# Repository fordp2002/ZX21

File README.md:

# ZX21
40 Years after the Sinclair ZX81 was released this project aims to preserve the first 4 chip computer

This a computer presevation project for the [Sinclair ZX81](https://github.com/fordp2002/ZX21.git).

Features (Hopefully).

* Drop in replacement for a ZX81
* Built in 16K+ RAM, no need for a RAM Pack
* Built in Composite Video Output 
* Barrel Jack power input, center Positive
* OPTION: Single Joystick port (not compatible with quickfire etc.)
* OPTION: Switchable to 1K RAM
* OPTION: [Back Porch Support](http://zx.zigg.net/misc-projects/ZX81_Video_Conditioning.pdf) for early ULAs
* OPTION: Built in support for [ZX-Wespi](https://github.com/holmatic/zx-iot-mi)
* OPTION: [ZON-X](http://www.zx81stuff.org.uk/zx81/hardware/ZONX81) Compatible Yamaha YM2149F Based Sound
* OPTION: Switchable between Sinclair ROM OR [AT28C256 EEPROM](http://ww1.microchip.com/downloads/en/DeviceDoc/doc0006.pdf)
* OPTION: 16 Pin Box Header for DK'Tronics Keyboard

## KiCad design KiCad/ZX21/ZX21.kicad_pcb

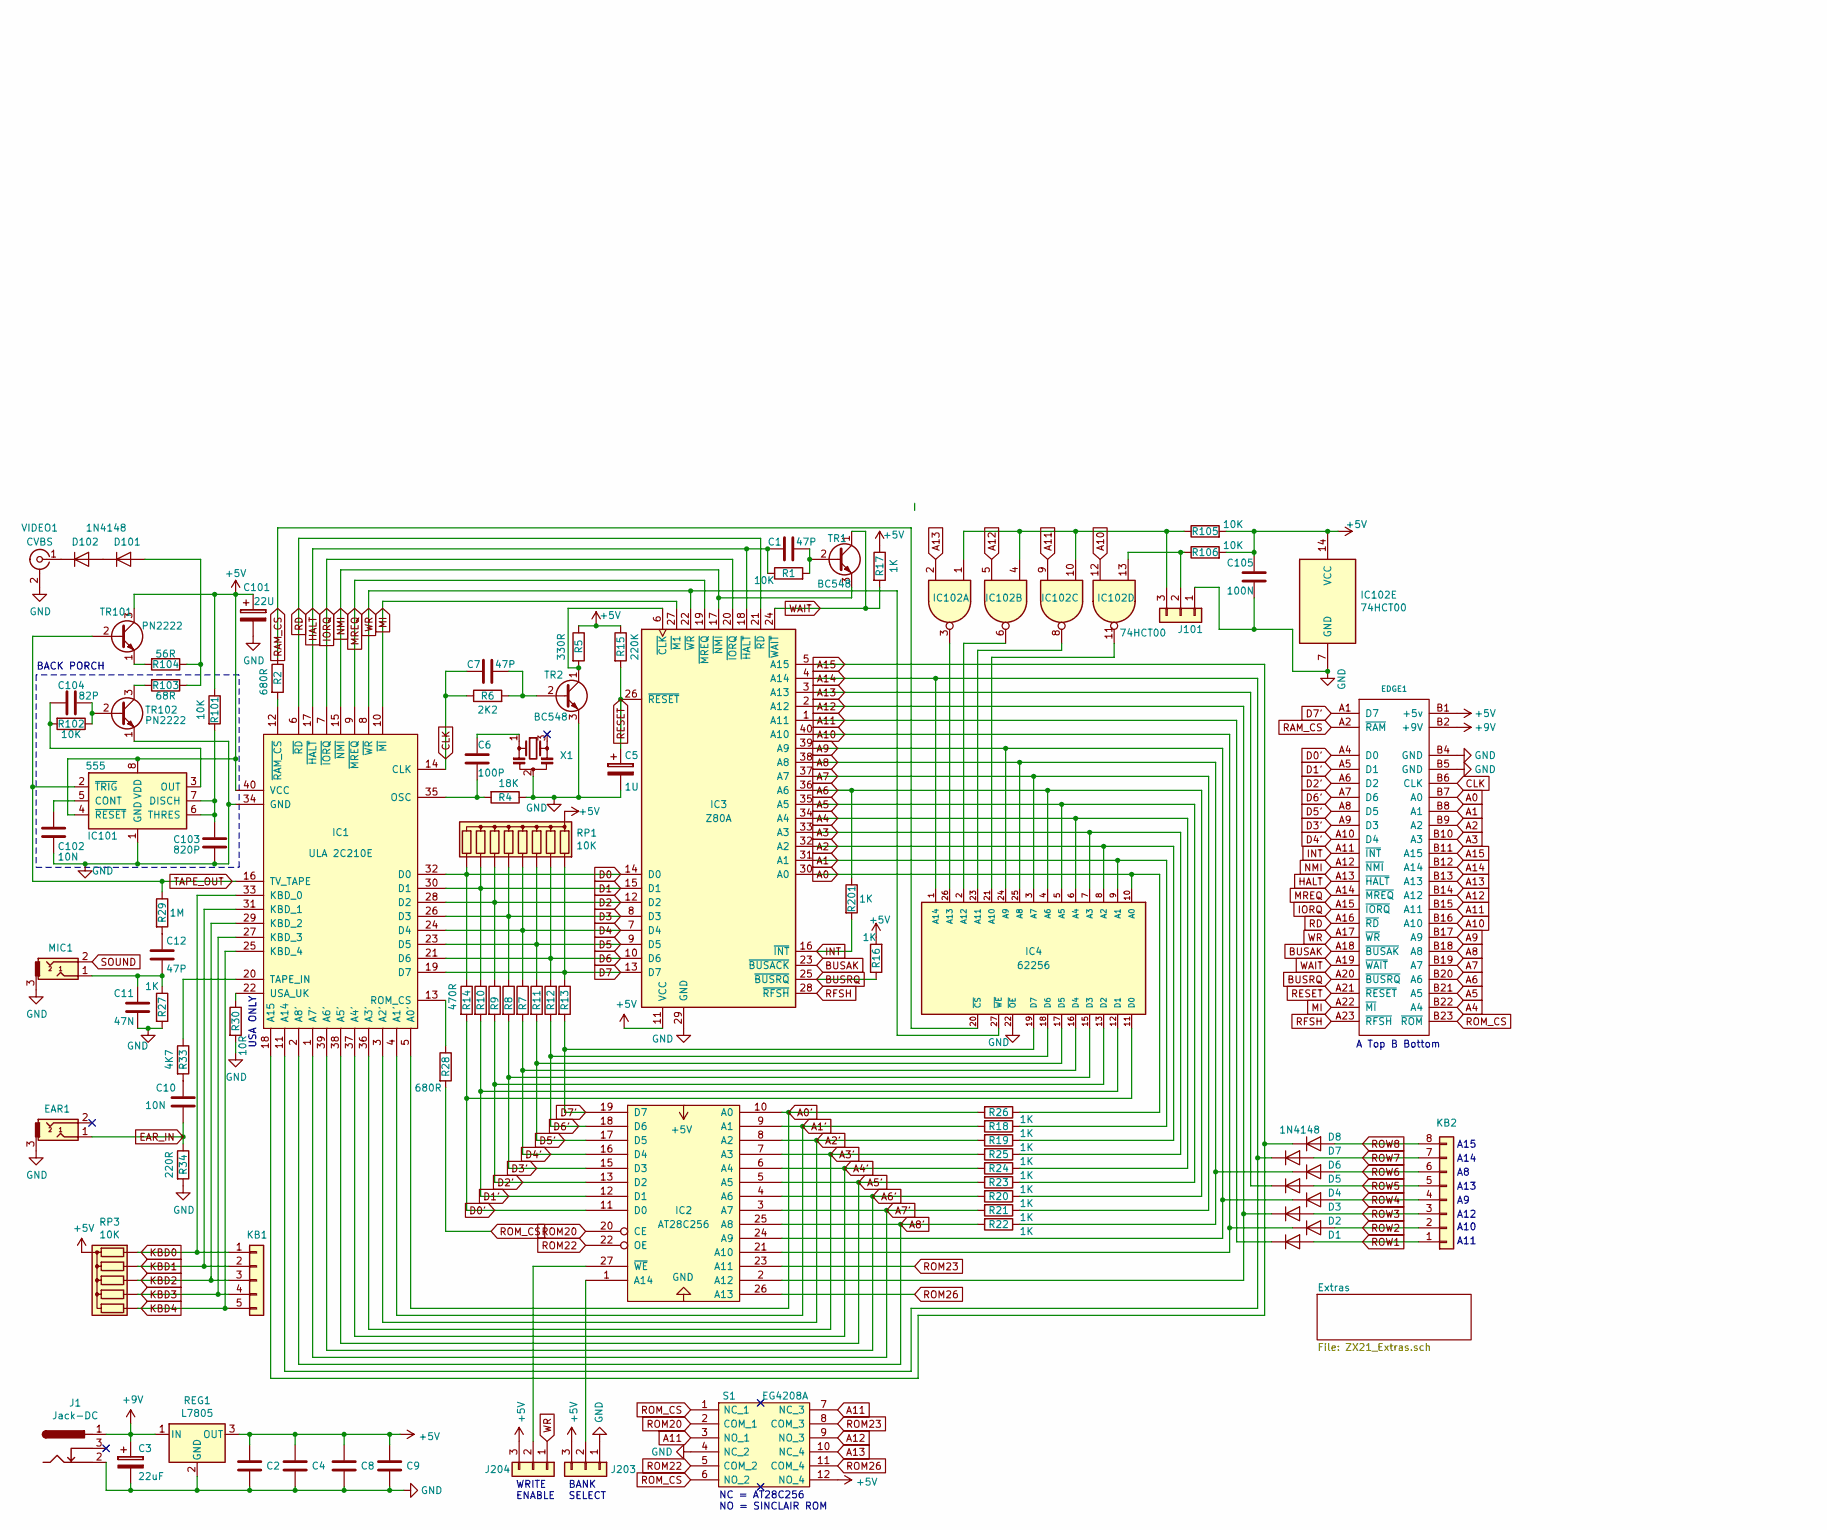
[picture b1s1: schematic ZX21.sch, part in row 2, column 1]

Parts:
C1: 47P; C_Disc_D3.0mm_W2.0mm_P2.50mm
C2: 100N; C_Disc_D5.0mm_W2.5mm_P2.50mm
C3: 22uF; CP_Axial_L11.0mm_D5.0mm_P18.00mm_Horizontal
C4, C9: 100N; C_Disc_D4.7mm_W2.5mm_P5.00mm
C5: 1U; CP_Radial_D5.0mm_P2.50mm
C6: 100P; C_Disc_D4.7mm_W2.5mm_P5.00mm
C7, C12: 47P; C_Disc_D4.7mm_W2.5mm_P5.00mm
C8, C10, C102: 10N; C_Disc_D4.7mm_W2.5mm_P5.00mm
C11: 47N; C_Disc_D4.7mm_W2.5mm_P5.00mm
C101: 22U; CP_Radial_D5.0mm_P2.50mm
C103: 820P; C_Disc_D4.7mm_W2.5mm_P5.00mm
C104: 82P; C_Disc_D4.7mm_W2.5mm_P5.00mm
C105: 100N; C_0603_HandSoldering
D1, D2, D3, D4, D5, D6, D7, D8, D101, D102: 1N4148; D_DO-35_SOD27_P7.62mm_Horizontal
EAR1: Audio-Jack-3; ASJ_125_3_3.5mm_Jack
EDGE1: ZX81BUS; ZX_Bus_Edge_Connector
IC1: ULA 2C210E; DIP-40_W15.24mm_Socket_LongPads
IC2: AT28C256; DIP-28_W15.24mm_Socket_LongPads
IC3: Z80A; DIP-40_W15.24mm_Socket_LongPads
IC4: 62256; DIP-28_W15.24mm_Socket_LongPads
IC101: 555; DIP-8_W7.62mm_Socket_LongPads
IC102: 74HCT00; SOIC-14_3.9x8.7mm_Pitch1.27mm
J1: Jack-DC; BARREL_JACK
J101, J203, J204: Conn_01x03; Pin_Header_Straight_1x03_Pitch2.54mm
KB1: Conn_01x05; Pin_Header_Straight_1x05_Pitch2.54mm
KB2: Conn_01x08; Pin_Header_Straight_1x08_Pitch2.54mm
MIC1: Audio-Jack-3; ASJ_125_3_3.5mm_Jack
R1, R101, R102: 10K; R_Axial_DIN0204_L3.6mm_D1.6mm_P7.62mm_Horizontal
R2, R28: 680R; R_Axial_DIN0204_L3.6mm_D1.6mm_P7.62mm_Horizontal
R4: 18K; R_Axial_DIN0204_L3.6mm_D1.6mm_P7.62mm_Horizontal
R5: 330R; R_Axial_DIN0204_L3.6mm_D1.6mm_P7.62mm_Horizontal
R6: 2K2; R_Axial_DIN0204_L3.6mm_D1.6mm_P7.62mm_Horizontal
R7, R8, R9, R10, R11, R12, R13, R14: 470R; R_Axial_DIN0204_L3.6mm_D1.6mm_P7.62mm_Horizontal
R15: 220K; R_Axial_DIN0204_L3.6mm_D1.6mm_P7.62mm_Horizontal
R16, R17, R18, R19, R20, R21, R22, R23, R24, R25, R26, R27, R201: 1K; R_Axial_DIN0204_L3.6mm_D1.6mm_P7.62mm_Horizontal
R29: 1M; R_Axial_DIN0204_L3.6mm_D1.6mm_P7.62mm_Horizontal
R30: 10R; R_Axial_DIN0204_L3.6mm_D1.6mm_P7.62mm_Horizontal
R33: 4K7; R_Axial_DIN0204_L3.6mm_D1.6mm_P7.62mm_Horizontal
R34: 220R; R_Axial_DIN0204_L3.6mm_D1.6mm_P7.62mm_Horizontal
R103: 68R; R_Axial_DIN0204_L3.6mm_D1.6mm_P7.62mm_Horizontal
R104: 56R; R_Axial_DIN0204_L3.6mm_D1.6mm_P7.62mm_Horizontal
R105, R106: 10K; R_0603_HandSoldering
REG1: L7805; TO-220-3_Horizontal
RP1: 10K; R_Array_SIP9
RP3: 10K; R_Array_SIP6
S1: EG4208A; EG4208; Manufacturer_Part_Number EG4208A; Mouser Part Number 612-EG4208A
TR1, TR2: BC548; TO-92_Molded_Narrow
TR101, TR102: PN2222; TO-92_Molded_Narrow
VIDEO1: CVBS; YELLOW_RCA
X1: 3.5MHz; Resonator-3pin_w7.0mm_h2.5mm

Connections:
+5V: C2.1, C4.1, C8.1, C9.1, C101.1, C105.1, EDGE1.B1 (+5v), IC1.40 (VCC), IC2.28 (VCC), IC3.11 (VCC), IC4.28 (VCC), IC101.4 (~RESET), IC101.8 (VDD), IC102.14 (VCC), J203.3, J204.3, R5.1, R15.1, R16.2, R17.1, R101.1, R105.2, R106.2, REG1.3 (OUT), RP1.1 (common), RP3.1 (common), S1.12 (NO_4), TR101.3 (C); also elsewhere on the board
+9V: C3.1, EDGE1.B2 (+9V), J1.1, REG1.1 (IN); also elsewhere on the board
A0: EDGE1.B7 (A0), IC3.30 (A0), IC4.10 (A0), R26.1; also elsewhere on the board
A0': IC1.5 (A0'), IC2.10 (A0), R26.2; also elsewhere on the board
A1: EDGE1.B8 (A1), IC3.31 (A1), IC4.9 (A1), R18.1; also elsewhere on the board
A1': IC1.4 (A1'), IC2.9 (A1), R18.2; also elsewhere on the board
A2: EDGE1.B9 (A2), IC3.32 (A2), IC4.8 (A2), R19.1; also elsewhere on the board
A2': IC1.3 (A2'), IC2.8 (A2), R19.2; also elsewhere on the board
A3: EDGE1.B10 (A3), IC3.33 (A3), IC4.7 (A3), R25.1; also elsewhere on the board
A3': IC1.36 (A3'), IC2.7 (A3), R25.2; also elsewhere on the board
A4: EDGE1.B22 (A4), IC3.34 (A4), IC4.6 (A4), R24.1; also elsewhere on the board
A4': IC1.37 (A4'), IC2.6 (A4), R24.2; also elsewhere on the board
A5: EDGE1.B21 (A5), IC3.35 (A5), IC4.5 (A5), R23.1; also elsewhere on the board
A5': IC1.38 (A5'), IC2.5 (A5), R23.2; also elsewhere on the board
A6: EDGE1.B20 (A6), IC3.36 (A6), IC4.4 (A6), R20.1, R201.1; also elsewhere on the board
A6': IC1.39 (A6'), IC2.4 (A6), R20.2; also elsewhere on the board
A7: EDGE1.B19 (A7), IC3.37 (A7), IC4.3 (A7), R21.1; also elsewhere on the board
A7': IC1.1 (A7'), IC2.3 (A7), R21.2; also elsewhere on the board
A8: D6.1 (K), EDGE1.B18 (A8), IC3.38 (A8), IC4.25 (A8), R22.1; also elsewhere on the board
A8': IC1.2 (A8'), IC2.25 (A8), R22.2; also elsewhere on the board
A9: D4.1 (K), EDGE1.B17 (A9), IC2.24 (A9), IC3.39 (A9), IC4.24 (A9); also elsewhere on the board
A10: D2.1 (K), EDGE1.B16 (A10), IC2.21 (A10), IC3.40 (A10), IC102.12; also elsewhere on the board
A11: D1.1 (K), EDGE1.B15 (A11), IC3.1 (A11), IC102.9, S1.3 (NO_1), S1.7 (NC_3); also elsewhere on the board
A12: D3.1 (K), EDGE1.B14 (A12), IC2.2 (A12), IC3.2 (A12), IC102.5, S1.9 (NO_3); also elsewhere on the board
A13: D5.1 (K), EDGE1.B13 (A13), IC3.3 (A13), IC102.2, S1.10 (NC_4); also elsewhere on the board
A14: D7.1 (K), EDGE1.B12 (A14), IC1.11 (A14), IC3.4 (A14), IC4.1 (A14); also elsewhere on the board
A15: D8.1 (K), EDGE1.B11 (A15), IC1.18 (A15), IC3.5 (A15); also elsewhere on the board
BUSAK: EDGE1.A18 (~BUSAK), IC3.23 (~BUSACK); also elsewhere on the board
BUSRQ: EDGE1.A20 (~BUSRQ), IC3.25 (~BUSRQ), R16.1; also elsewhere on the board
CLK: C7.2, EDGE1.B6 (CLK), IC1.14 (CLK), R6.1; also elsewhere on the board
D0: IC1.32 (D0), IC3.14 (D0), R14.1, RP1.9 (R8); also elsewhere on the board
D0': EDGE1.A4 (D0), IC2.11 (D0), IC4.11 (D0), R14.2; also elsewhere on the board
D1: IC1.30 (D1), IC3.15 (D1), R10.1, RP1.8 (R7); also elsewhere on the board
D1': EDGE1.A5 (D1), IC2.12 (D1), IC4.12 (D1), R10.2; also elsewhere on the board
D2: IC1.28 (D2), IC3.12 (D2), R9.1, RP1.7 (R6); also elsewhere on the board
D2': EDGE1.A6 (D2), IC2.13 (D2), IC4.13 (D2), R9.2; also elsewhere on the board
D3: IC1.26 (D3), IC3.8 (D3), R8.1, RP1.6 (R5); also elsewhere on the board
D3': EDGE1.A9 (D3), IC2.15 (D3), IC4.15 (D3), R8.2; also elsewhere on the board
D4: IC1.24 (D4), IC3.7 (D4), R7.1, RP1.5 (R4); also elsewhere on the board
D4': EDGE1.A10 (D4), IC2.16 (D4), IC4.16 (D4), R7.2; also elsewhere on the board
D5: IC1.23 (D5), IC3.9 (D5), R11.1, RP1.4 (R3); also elsewhere on the board
D5': EDGE1.A8 (D5), IC2.17 (D5), IC4.17 (D5), R11.2; also elsewhere on the board
D6: IC1.21 (D6), IC3.10 (D6), R12.2, RP1.3 (R2); also elsewhere on the board
D6': EDGE1.A7 (D6), IC2.18 (D6), IC4.18 (D6), R12.1; also elsewhere on the board
D7: IC1.19 (D7), IC3.13 (D7), R13.1, RP1.2 (R1); also elsewhere on the board
D7': EDGE1.A1 (D7), IC2.19 (D7), IC4.19 (D7), R13.2; also elsewhere on the board
EAR_IN: C10.2, EAR1.1, R34.1; also elsewhere on the board
GND: C2.2, C3.2, C4.2, C5.2, C8.2, C9.2, C11.2, C101.2, C102.2, C103.2, C105.2, EAR1.3, EDGE1.B4 (GND), EDGE1.B5 (GND), IC1.34 (GND), IC2.14 (GND), IC3.29 (GND), IC4.14 (GND), IC4.22 (~OE), IC101.1 (GND), IC102.7 (GND), J1.2, J101.1, J203.1, MIC1.3, R4.1, R27.2, R30.2, R34.2, REG1.2 (GND), S1.4 (NC_2), TR2.3 (E), TR102.1 (E), VIDEO1.2 (Ext), X1.2; also elsewhere on the board
HALT: C1.2, EDGE1.A13 (~HALT), IC1.17 (~HALT), IC3.18 (~HALT), R1.1; also elsewhere on the board
INT: EDGE1.A11 (~INT), IC3.16 (~INT), R201.2; also elsewhere on the board
IORQ: EDGE1.A15 (~IORQ), IC1.7 (~IORQ), IC3.20 (~IORQ); also elsewhere on the board
KBD0: IC1.33 (KBD_0), KB1.1, RP3.2 (R1); also elsewhere on the board
KBD1: IC1.31 (KBD_1), KB1.2, RP3.3 (R2); also elsewhere on the board
KBD2: IC1.29 (KBD_2), KB1.3, RP3.4 (R3); also elsewhere on the board
KBD3: IC1.27 (KBD_3), KB1.4, RP3.5 (R4); also elsewhere on the board
KBD4: IC1.25 (KBD_4), KB1.5, RP3.6 (R5); also elsewhere on the board
MI: EDGE1.A22 (~MI), IC1.10 (~MI), IC3.27 (~M1~); also elsewhere on the board
MREQ: EDGE1.A14 (~MREQ), IC1.9 (~MREQ), IC3.19 (~MREQ); also elsewhere on the board
NMI: EDGE1.A12 (~NMI), IC1.15 (~NMI), IC3.17 (~NMI), TR1.3 (E); also elsewhere on the board
unnamed: C1.1, R1.2, TR1.2 (B)
unnamed: C6.1, X1.1
unnamed: C6.2, IC1.35 (OSC), R4.2
unnamed: C7.1, R6.2, TR2.2 (B)
unnamed: C10.1, R33.2
unnamed: C11.1, C12.2, MIC1.1, R27.1
unnamed: C12.1, R29.2
unnamed: C102.1, IC101.5 (CONT)
unnamed: C103.1, IC101.6 (THRES), IC101.7 (DISCH), R101.2
unnamed: C104.1, IC101.3 (OUT), R102.2
unnamed: C104.2, R102.1, TR102.2 (B)
unnamed: D101.1 (K), D102.2 (A)
unnamed: D101.2 (A), R103.1, R104.1
unnamed: D102.1 (K), VIDEO1.1 (In)
unnamed: IC1.12 (~RAM_CS), R2.2
unnamed: IC1.13 (ROM_CS), R28.1
unnamed: IC1.20 (TAPE_IN), R33.1
unnamed: IC1.22 (USA_UK), R30.1
unnamed: IC2.1 (A14), J203.2
unnamed: IC2.27 (~WE), J204.2
unnamed: IC3.6 (~CLK), R5.2, TR2.1 (C)
unnamed: IC102.1, IC102.4, IC102.10, J101.3, R105.1
unnamed: IC4.26 (A13), IC102.3
unnamed: IC4.2 (A12), IC102.6
unnamed: IC4.23 (A11), IC102.8
unnamed: IC4.21 (A10), IC102.11
unnamed: IC102.13, J101.2, R106.1
unnamed: R103.2, TR102.3 (C)
unnamed: R104.2, TR101.1 (E)
RAM_CS: EDGE1.A2 (~RAM), IC4.20 (~CS), R2.1; also elsewhere on the board
RD: EDGE1.A16 (~RD), IC1.6 (~RD), IC3.21 (~RD); also elsewhere on the board
RESET: C5.1, EDGE1.A21 (~RESET), IC3.26 (~RESET), R15.2; also elsewhere on the board
RFSH: EDGE1.A23 (~RFSH), IC3.28 (~RFSH); also elsewhere on the board
ROM20: IC2.20 (CE), S1.2 (COM_1)
ROM22: IC2.22 (OE), S1.5 (COM_2)
ROM23: IC2.23 (A11), S1.8 (COM_3)
ROM26: IC2.26 (A13), S1.11 (COM_4)
ROM_CS: EDGE1.B23 (~ROM), R28.2, S1.1 (NC_1), S1.6 (NO_2); also elsewhere on the board
ROW1: D1.2 (A), KB2.1; also elsewhere on the board
ROW2: D2.2 (A), KB2.2; also elsewhere on the board
ROW3: D3.2 (A), KB2.3; also elsewhere on the board
ROW4: D4.2 (A), KB2.4; also elsewhere on the board
ROW5: D5.2 (A), KB2.5; also elsewhere on the board
ROW6: D6.2 (A), KB2.6; also elsewhere on the board
ROW7: D7.2 (A), KB2.7; also elsewhere on the board
ROW8: D8.2 (A), KB2.8; also elsewhere on the board
SOUND: MIC1.2; also elsewhere on the board
TAPE_OUT: IC1.16 (TV_TAPE), IC101.2 (~TRIG), R29.1, TR101.2 (B); also elsewhere on the board
WAIT: EDGE1.A19 (~WAIT), IC3.24 (~WAIT~), R17.2, TR1.1 (C); also elsewhere on the board
WR: EDGE1.A17 (~WR), IC1.8 (~WR), IC3.22 (~WR), IC4.27 (~WE), J204.1; also elsewhere on the board

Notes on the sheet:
BANK SELECT
WRITE ENABLE
A Top B Bottom
USA ONLY
A11
A10
A12
A13
A14
A15
NC = AT28C256 NO = SINCLAIR ROM
BACK PORCH

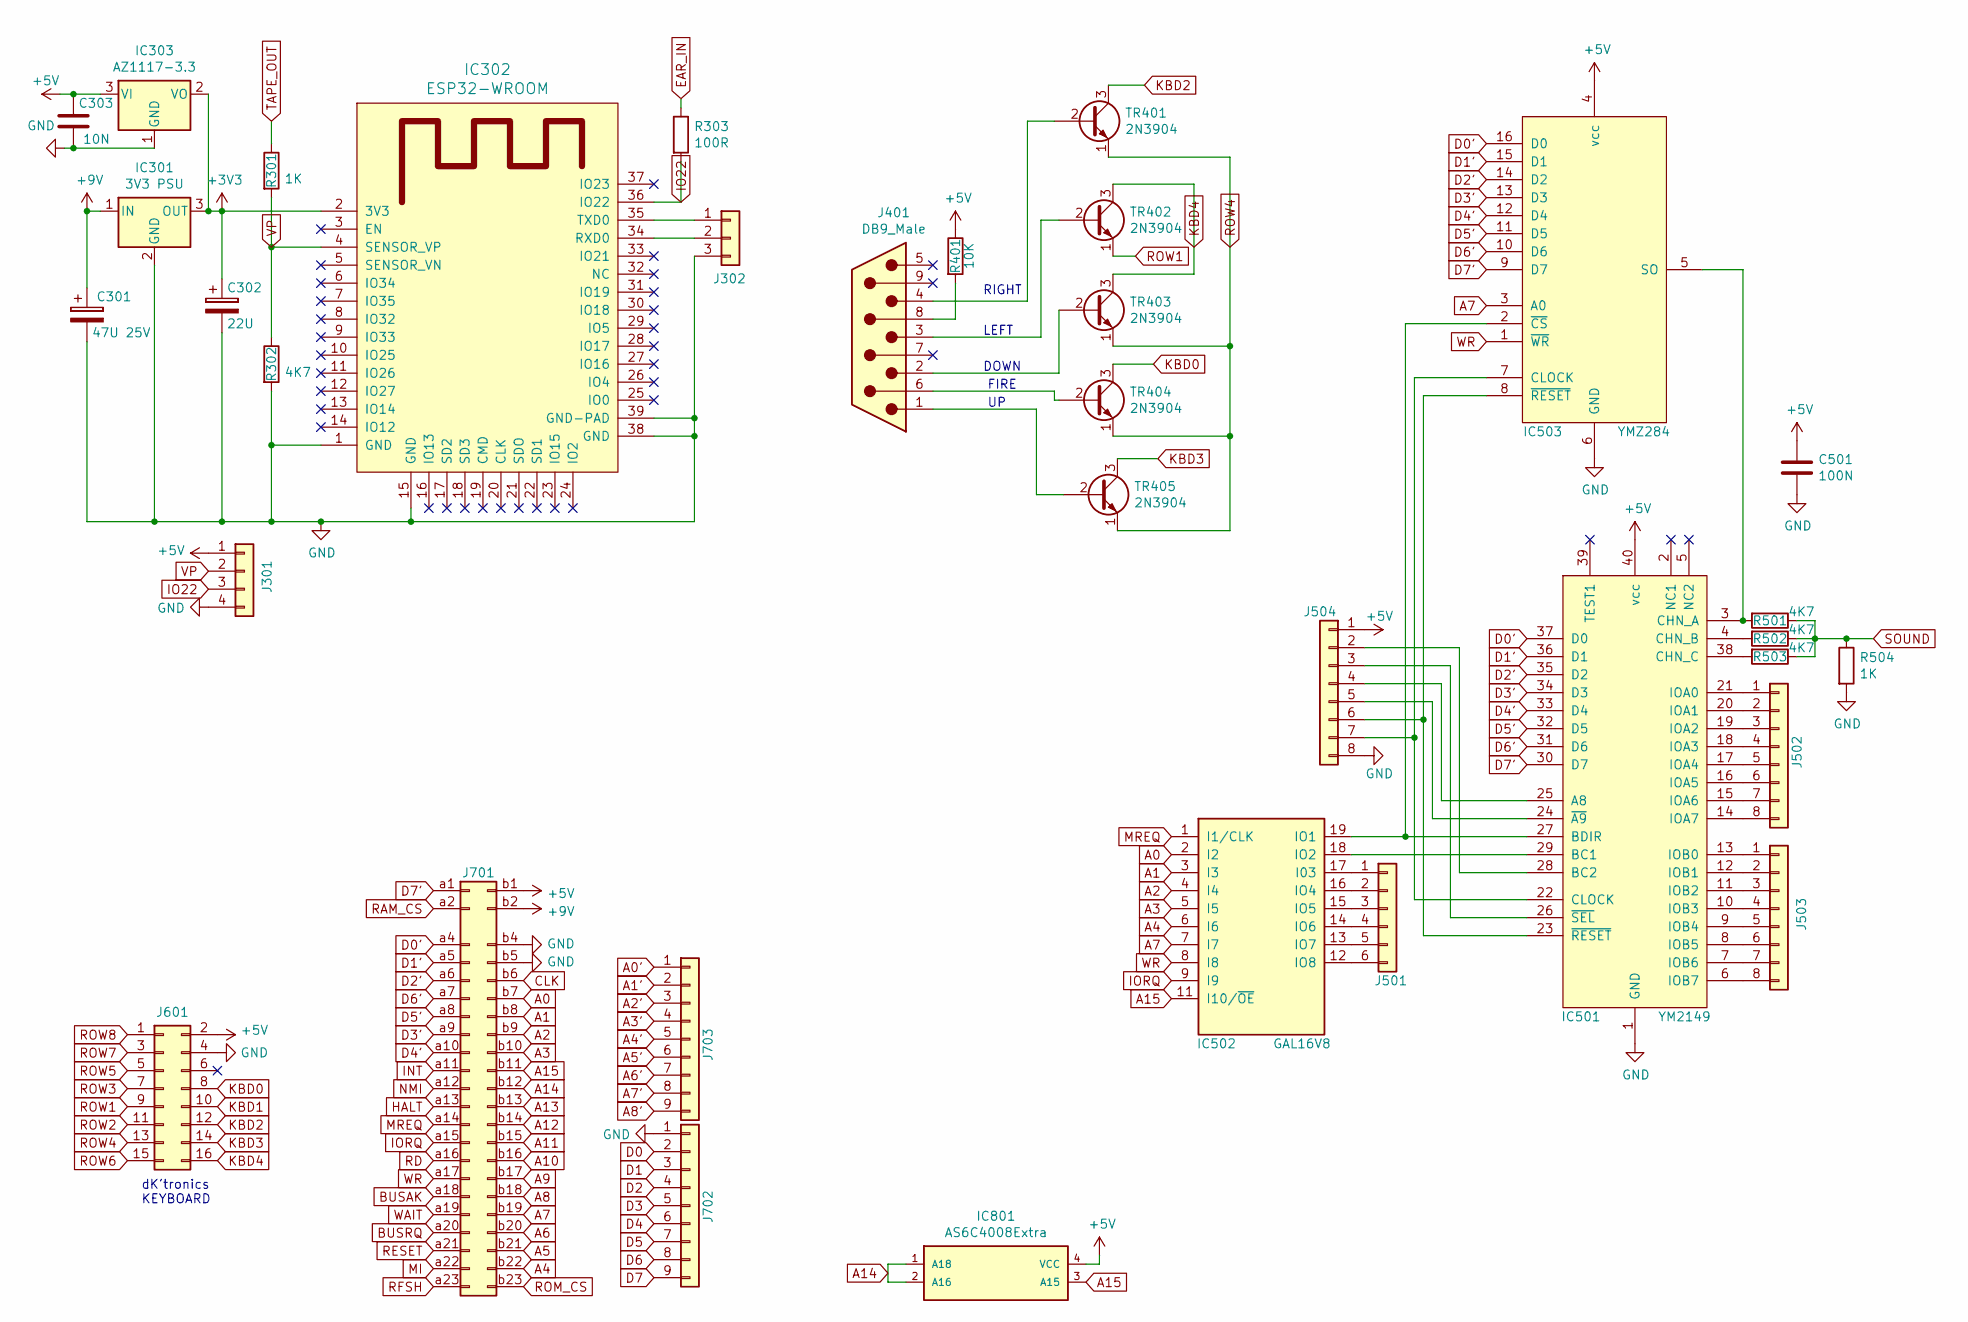
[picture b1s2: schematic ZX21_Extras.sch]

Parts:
C301: 47U 25V; CP_Radial_D5.0mm_P2.50mm
C302: 22U; CP_Radial_D5.0mm_P2.50mm
C303: 10N; C_0603_HandSoldering
C501: 100N; C_Disc_D4.7mm_W2.5mm_P5.00mm
IC301: 3V3 PSU; TO-220-3_Horizontal
IC302: ESP32-WROOM
IC303: AZ1117-3.3; SOT-23_Handsoldering
IC501: YM2149; DIP-40_W15.24mm_Socket_LongPads
IC502: GAL16V8; DIP-20_W7.62mm_Socket_LongPads
IC503: YMZ284; DIP-16_W7.62mm_Socket_LongPads
IC801: AS6C4008Extra; DIP-4_W15.24mm_Socket_LongPads
J301: Conn_01x04; Pin_Header_Straight_1x04_Pitch2.54mm
J302: Conn_01x03; Pin_Header_Straight_1x03_Pitch2.54mm
J401: DB9_Male; DB9MC
J501: Conn_01x06; Pin_Header_Straight_1x06_Pitch2.54mm
J502, J503, J504: Conn_01x08; Pin_Header_Straight_1x08_Pitch2.54mm
J601: Conn_02x08_Odd_Even; IDC_Header_Straight_16pins
J701: Conn_02x23_Row_Letter_First; Pin_Header_Straight_2x23_Pitch2.54mm
J702, J703: Conn_01x09; Pin_Header_Straight_1x09_Pitch2.54mm
R301, R504: 1K; R_Axial_DIN0204_L3.6mm_D1.6mm_P7.62mm_Horizontal
R302, R501, R502, R503: 4K7; R_Axial_DIN0204_L3.6mm_D1.6mm_P7.62mm_Horizontal
R303: 100R; R_Axial_DIN0204_L3.6mm_D1.6mm_P7.62mm_Horizontal
R401: 10K; R_Axial_DIN0204_L3.6mm_D1.6mm_P7.62mm_Horizontal
TR401, TR402, TR403, TR404, TR405: 2N3904; TO-92_Molded_Narrow

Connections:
+3V3: C302.1, IC301.3 (OUT), IC302.2 (3V3), IC303.2 (VO)
+5V: C303.1, C501.1, IC303.3 (VI), IC501.40 (vcc), IC502.20 (VCC), IC503.4 (vcc), IC801.4 (VCC), J301.1, J504.1, J601.2, J701.b1, R401.1; also elsewhere on the board
+9V: C301.1, IC301.1 (IN), J701.b2; also elsewhere on the board
A0: IC502.2 (I2), J701.b7; also elsewhere on the board
A0': J703.1; also elsewhere on the board
A1: IC502.3 (I3), J701.b8; also elsewhere on the board
A1': J703.2; also elsewhere on the board
A2: IC502.4 (I4), J701.b9; also elsewhere on the board
A2': J703.3; also elsewhere on the board
A3: IC502.5 (I5), J701.b10; also elsewhere on the board
A3': J703.4; also elsewhere on the board
A4: IC502.6 (I6), J701.b22; also elsewhere on the board
A4': J703.5; also elsewhere on the board
A5: J701.b21; also elsewhere on the board
A5': J703.6; also elsewhere on the board
A6: J701.b20; also elsewhere on the board
A6': J703.7; also elsewhere on the board
A7: IC502.7 (I7), IC503.3 (A0), J701.b19; also elsewhere on the board
A7': J703.8; also elsewhere on the board
A8: J701.b18; also elsewhere on the board
A8': J703.9; also elsewhere on the board
A9: J701.b17; also elsewhere on the board
A10: J701.b16; also elsewhere on the board
A11: J701.b15; also elsewhere on the board
A12: J701.b14; also elsewhere on the board
A13: J701.b13; also elsewhere on the board
A14: IC801.1 (A18), IC801.2 (A16), J701.b12; also elsewhere on the board
A15: IC502.11 (I10/~OE~), IC801.3 (A15), J701.b11; also elsewhere on the board
BUSAK: J701.a18; also elsewhere on the board
BUSRQ: J701.a20; also elsewhere on the board
CLK: J701.b6; also elsewhere on the board
D0: J702.2; also elsewhere on the board
D0': IC501.37 (D0), IC503.16 (D0), J701.a4; also elsewhere on the board
D1: J702.3; also elsewhere on the board
D1': IC501.36 (D1), IC503.15 (D1), J701.a5; also elsewhere on the board
D2: J702.4; also elsewhere on the board
D2': IC501.35 (D2), IC503.14 (D2), J701.a6; also elsewhere on the board
D3: J702.5; also elsewhere on the board
D3': IC501.34 (D3), IC503.13 (D3), J701.a9; also elsewhere on the board
D4: J702.6; also elsewhere on the board
D4': IC501.33 (D4), IC503.12 (D4), J701.a10; also elsewhere on the board
D5: J702.7; also elsewhere on the board
D5': IC501.32 (D5), IC503.11 (D5), J701.a8; also elsewhere on the board
D6: J702.8; also elsewhere on the board
D6': IC501.31 (D6), IC503.10 (D6), J701.a7; also elsewhere on the board
D7: J702.9; also elsewhere on the board
D7': IC501.30 (D7), IC503.9 (D7), J701.a1; also elsewhere on the board
EAR_IN: R303.1; also elsewhere on the board
GND: C301.2, C302.2, C303.2, C501.2, IC301.2 (GND), IC302.1 (GND), IC302.15 (GND), IC302.38 (GND), IC302.39 (GND-PAD), IC303.1 (GND), IC501.1 (GND), IC502.10 (GND), IC503.6 (GND), J301.4, J302.3, J504.8, J601.4, J701.b4, J701.b5, J702.1, R302.2, R504.2; also elsewhere on the board
HALT: J701.a13; also elsewhere on the board
INT: J701.a11; also elsewhere on the board
IO22: IC302.36 (IO22), J301.3, R303.2
IORQ: IC502.9 (I9), J701.a15; also elsewhere on the board
KBD0: J601.8, TR404.3 (C); also elsewhere on the board
KBD1: J601.10; also elsewhere on the board
KBD2: J601.12, TR401.3 (C); also elsewhere on the board
KBD3: J601.14, TR405.3 (C); also elsewhere on the board
KBD4: J601.16, TR402.3 (C), TR403.3 (C); also elsewhere on the board
MI: J701.a22; also elsewhere on the board
MREQ: IC502.1 (I1/CLK), J701.a14; also elsewhere on the board
NMI: J701.a12; also elsewhere on the board
unnamed: IC302.34 (RXD0), J302.2
unnamed: IC302.35 (TXD0), J302.1
unnamed: IC501.3 (CHN_A), IC503.5 (SO), R501.2
unnamed: IC501.4 (CHN_B), R502.2
unnamed: IC501.6 (IOB7), J503.8
unnamed: IC501.7 (IOB6), J503.7
unnamed: IC501.8 (IOB5), J503.6
unnamed: IC501.9 (IOB4), J503.5
unnamed: IC501.10 (IOB3), J503.4
unnamed: IC501.11 (IOB2), J503.3
unnamed: IC501.12 (IOB1), J503.2
unnamed: IC501.13 (IOB0), J503.1
unnamed: IC501.14 (IOA7), J502.8
unnamed: IC501.15 (IOA6), J502.7
unnamed: IC501.16 (IOA5), J502.6
unnamed: IC501.17 (IOA4), J502.5
unnamed: IC501.18 (IOA3), J502.4
unnamed: IC501.19 (IOA2), J502.3
unnamed: IC501.20 (IOA1), J502.2
unnamed: IC501.21 (IOA0), J502.1
unnamed: IC501.22 (CLOCK), IC503.7 (CLOCK), J504.7
unnamed: IC501.23 (~RESET), IC503.8 (~RESET), J504.6
unnamed: IC501.24 (~A9), J504.5
unnamed: IC501.25 (A8), J504.4
unnamed: IC501.26 (~SEL), J504.3
unnamed: IC501.27 (BDIR), IC502.19 (IO1), IC503.2 (~CS)
unnamed: IC501.28 (BC2), J504.2
unnamed: IC501.29 (BC1), IC502.18 (IO2)
unnamed: IC501.38 (CHN_C), R503.2
unnamed: IC502.12 (IO8), J501.6
unnamed: IC502.13 (IO7), J501.5
unnamed: IC502.14 (IO6), J501.4
unnamed: IC502.15 (IO5), J501.3
unnamed: IC502.16 (IO4), J501.2
unnamed: IC502.17 (I03), J501.1
unnamed: J401.1, TR405.2 (B)
unnamed: J401.2, TR403.2 (B)
unnamed: J401.3, TR402.2 (B)
unnamed: J401.4, TR401.2 (B)
unnamed: J401.6, TR404.2 (B)
unnamed: J401.8, R401.2
RAM_CS: J701.a2; also elsewhere on the board
RD: J701.a16; also elsewhere on the board
RESET: J701.a21; also elsewhere on the board
RFSH: J701.a23; also elsewhere on the board
ROM_CS: J701.b23; also elsewhere on the board
ROW1: J601.9, TR402.1 (E); also elsewhere on the board
ROW2: J601.11; also elsewhere on the board
ROW3: J601.7; also elsewhere on the board
ROW4: J601.13, TR401.1 (E), TR403.1 (E), TR404.1 (E), TR405.1 (E); also elsewhere on the board
ROW5: J601.5; also elsewhere on the board
ROW6: J601.15; also elsewhere on the board
ROW7: J601.3; also elsewhere on the board
ROW8: J601.1; also elsewhere on the board
SOUND: R501.1, R502.1, R503.1, R504.1; also elsewhere on the board
TAPE_OUT: R301.1; also elsewhere on the board
VP: IC302.4 (SENSOR_VP), J301.2, R301.2, R302.1
WAIT: J701.a19; also elsewhere on the board
WR: IC502.8 (I8), IC503.1 (~WR), J701.a17; also elsewhere on the board

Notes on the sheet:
RIGHT
LEFT
DOWN
FIRE
dK'tronics KEYBOARD

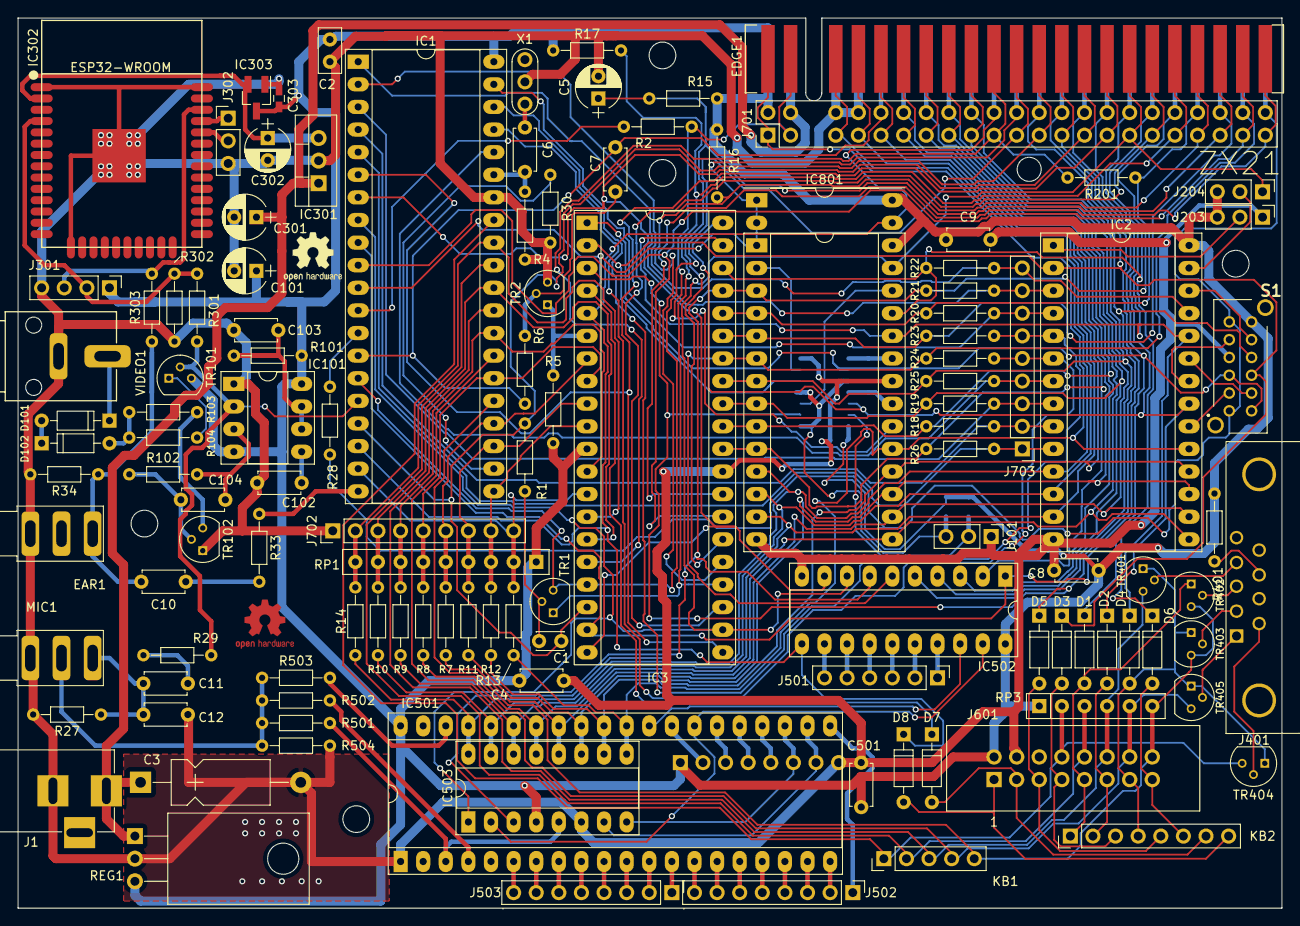
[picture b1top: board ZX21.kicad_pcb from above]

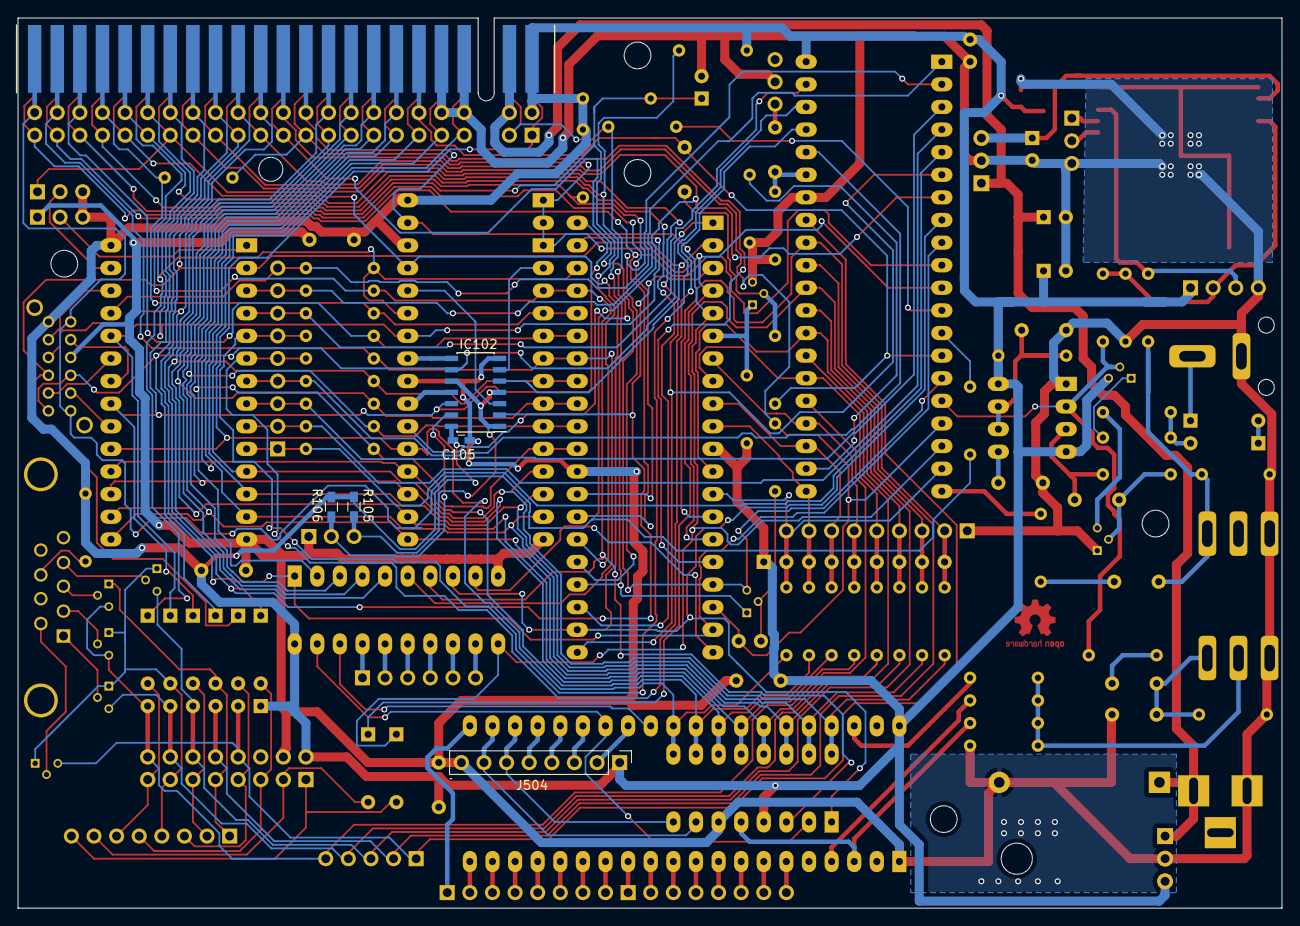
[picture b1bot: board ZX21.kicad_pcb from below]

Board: 2 copper layers, 142.0 x 100.0 mm, 125 parts (5 on the bottom side), 153 nets.

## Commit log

2020-11-21 Expand the Readme
2020-11-21 Upload some data sheets
2020-11-24 Main Sheet complete
2020-11-24 Start Extras
2020-11-25 Extras first draft
2020-11-25 Fixed most ERC Issues
2020-11-26 Layout Started
2020-11-26 Diodes fixed
2020-11-26 Added mounring holes
2020-11-26 Placement getting there
2020-11-27 Add Gate
2020-11-27 Part way through routing
2020-11-28 Yet more routing!
2020-11-28 Even more routing
2020-11-28 3 SD working better
2020-11-29 Yup more routing
2020-11-30 Added option for YMZ284 :D
2020-12-01 Routed!
2020-12-01 Tidy Up
2020-12-01 Into DRC
2020-12-02 Fixing DRC Issues
2020-12-04 FIrst go at DRC complete
2020-12-05 ESP32 Flipped
2020-12-05 Gerbers made
2020-12-11 Try to push interactive bom
2020-12-24 Latest update

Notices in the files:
KiCad/ZX21/ZX21.kicad_pcb:
Licence: BSD 3-Clause
